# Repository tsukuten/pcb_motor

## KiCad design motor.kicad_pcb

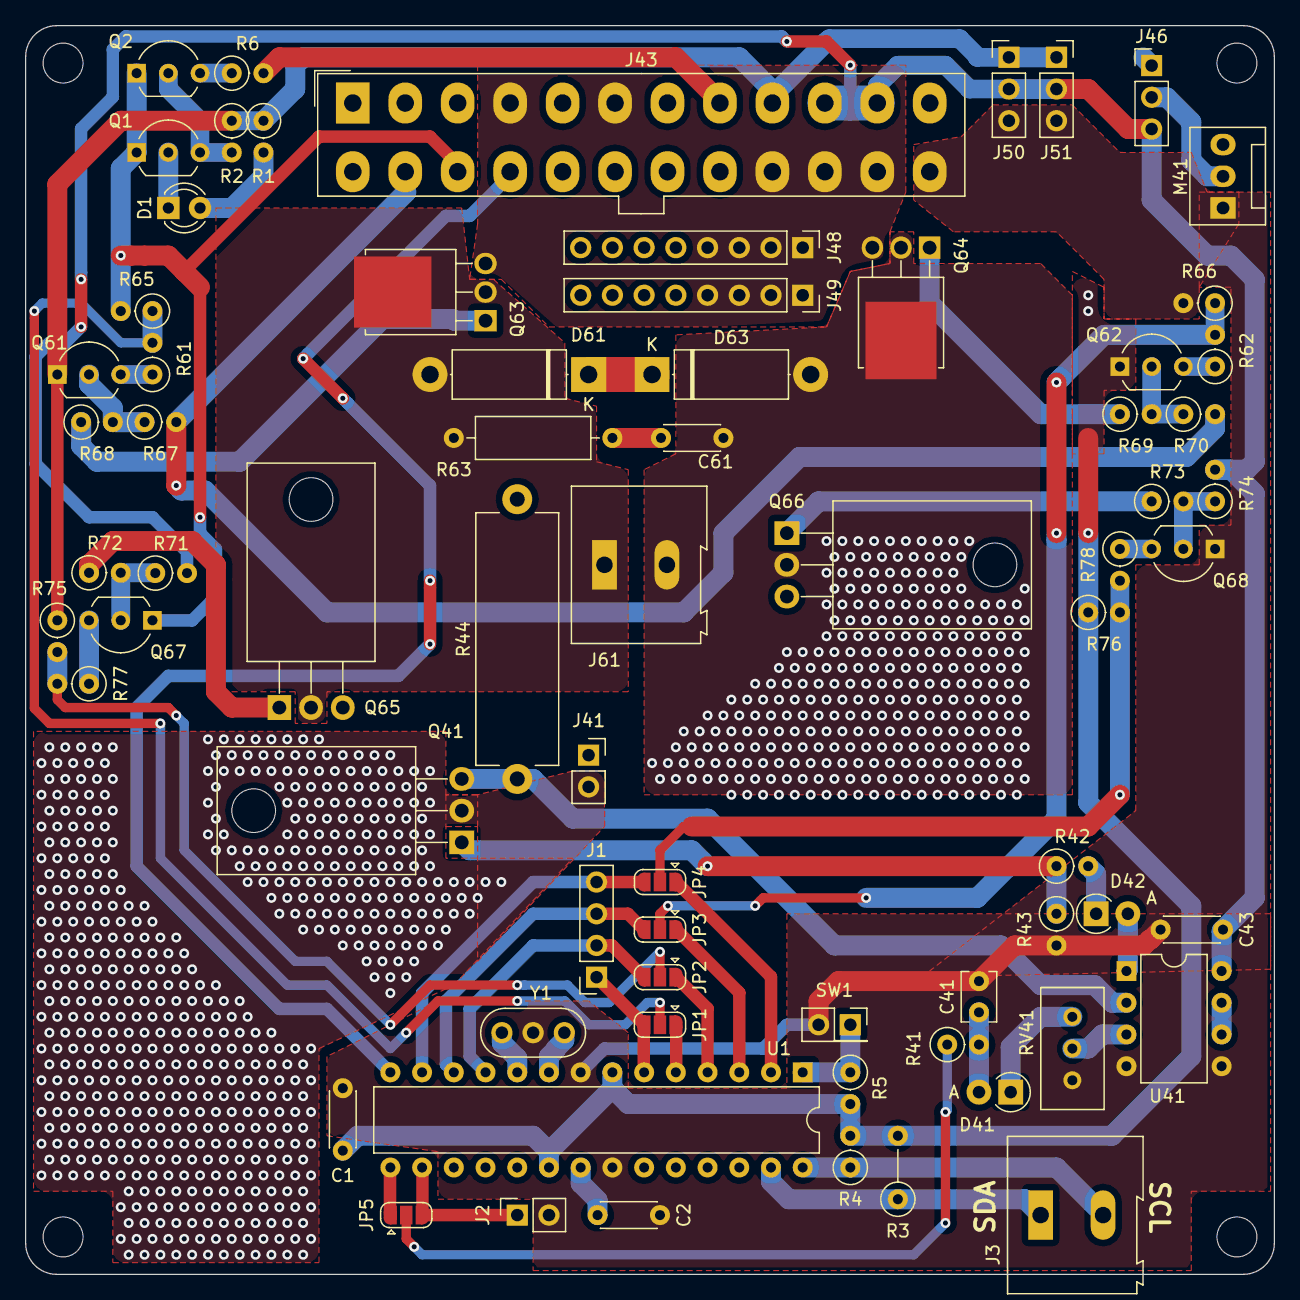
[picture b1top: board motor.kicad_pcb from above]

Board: 2 copper layers, 100.0 x 100.0 mm, 70 parts (0 on the bottom side), 59 nets.

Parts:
C1, C2, C43: 10u; C_Disc_D4.3mm_W1.9mm_P5.00mm
C41: 1u; C_Disc_D3.8mm_W2.6mm_P2.50mm
C61: C_snub_A; C_Disc_D4.3mm_W1.9mm_P5.00mm
D1: Power_NG; LED_D3.0mm
D41, D42: 1V0; D_T-1_P2.54mm_Vertical_AnodeUp
D61, D63: 1N5338B; D_5W_P12.70mm_Horizontal
J1: Gates_B; PinSocket_1x04_P2.54mm_Vertical
J2: PWM_B; PinSocket_1x02_P2.54mm_Vertical
J3: I2C; TerminalBlock_Altech_AK300-2_P5.00mm
J41: Jump_ID_A; PinSocket_1x02_P2.54mm_Vertical
J43: ATX_power; Molex_Mini-Fit_Jr_5566-24A_2x12_P4.20mm_Vertical
J46: Fan_vol_sel; PinHeader_1x03_P2.54mm_Vertical
J48: Power_male; PinHeader_1x08_P2.54mm_Vertical
J49: Power_female; PinSocket_1x08_P2.54mm_Vertical
J50: Power_signal_male; PinHeader_1x03_P2.54mm_Vertical
J51: Power_signal_female; PinSocket_1x03_P2.54mm_Vertical
J61: Motor_A; TerminalBlock_Altech_AK300-2_P5.00mm
JP1: Gate_sel_POS_P; SolderJumper-3_P1.3mm_Open_RoundedPad1.0x1.5mm
JP2: Gate_sel_POS_N; SolderJumper-3_P1.3mm_Open_RoundedPad1.0x1.5mm
JP3: Gate_sel_NEG_P; SolderJumper-3_P1.3mm_Open_RoundedPad1.0x1.5mm
JP4: Gate_sel_NEG_N; SolderJumper-3_P1.3mm_Open_RoundedPad1.0x1.5mm
JP5: PWM_sel; SolderJumper-3_P1.3mm_Open_RoundedPad1.0x1.5mm
M41: Fan_FET; FanPinHeader_1x03_P2.54mm_Vertical
Q1, Q2, Q67, Q68: 2SC1815; TO-92_Inline_Wide
Q41, Q65, Q66: EKI04027; TO-220-3_Horizontal_TabDown
Q61, Q62: 2SA1015; TO-92_Inline_Wide
Q63, Q64: IRFU5505; TO-251-3-1EP_Horizontal_TabDown
R1, R2, R6: 6k8; R_Axial_DIN0207_L6.3mm_D2.5mm_P2.54mm_Vertical
R3: 10k; R_Axial_DIN0207_L6.3mm_D2.5mm_P5.08mm_Vertical
R4, R5, R41, R67, R68, R69, R70, R71, R72, R73, R74: 10k; R_Axial_DIN0207_L6.3mm_D2.5mm_P2.54mm_Vertical
R42: 150; R_Axial_DIN0207_L6.3mm_D2.5mm_P2.54mm_Vertical
R43, R65, R66, R75, R76: 47k; R_Axial_DIN0207_L6.3mm_D2.5mm_P2.54mm_Vertical
R44: 0R33; R_Axial_Power_L20.0mm_W6.4mm_P22.40mm
R61, R62, R77, R78: 1k; R_Axial_DIN0207_L6.3mm_D2.5mm_P2.54mm_Vertical
R63: R_snub_A; R_Axial_DIN0309_L9.0mm_D3.2mm_P12.70mm_Horizontal
RV41: 10k; Potentiometer_Bourns_3296W_Vertical
SW1: Reset; PinSocket_2x01_P2.54mm_Vertical
U1: ATmega328P-PU; DIP-28_W7.62mm
U41: LM358; DIP-8_W7.62mm
Y1: 16MHz; Resonator-3Pin_W8.0mm_H3.5mm

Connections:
+5V: J43.4, J43.6, J43.21, J43.22, J43.23, J48.1, J48.2, J48.3, J48.4, J49.1, J49.2, J49.3, J49.4, Q63.3, Q64.3
+5VD: C1.1, J43.9, J46.1, J50.1, J51.1, Q61.1, Q62.1, R1.1, R2.1, R3.2, R4.2, R5.2, R75.1, R76.1, U1.7, U1.20
+12V: C43.1, J43.10, J43.11, J46.3, J50.2, J51.2, R71.2, R74.2, U41.8
-12V: J43.14, R67.2, R70.2
/Driver/Motor_A: D61.2, J61.1, Q63.2, Q63.4, Q65.2, R63.1
/Driver/Motor_~A~: C61.2, D63.2, J61.2, Q64.2, Q64.4, Q66.2
/Driver/V-: J41.1, Q65.3, Q66.3
/Gate_A_NEG_N: JP4.1, U1.2
/Gate_A_NEG_P: JP3.1, U1.3
/Gate_A_POS_N: JP2.1, U1.4
/Gate_A_POS_P: JP1.1, U1.5
/Gate_B_NEG_N: J1.4, JP4.3, U1.13
/Gate_B_NEG_P: J1.3, JP3.3, U1.12
/Gate_B_POS_N: J1.2, JP2.3, U1.11
/Gate_B_POS_P: J1.1, JP1.3, U1.6
/Gate_NEG_N: JP4.2, R76.2, R78.2
/Gate_NEG_P: JP3.2, R62.2, R66.1
/Gate_POS_N: JP2.2, R75.2, R77.2
/Gate_POS_P: JP1.2, R61.2, R65.1
/PWM: JP5.2, R41.1
/PWM_A: JP5.1, U1.15
/PWM_B: J2.1, JP5.3, U1.16
/PWR_OK: J43.8, R6.2
/SCL: J3.2, R4.1, U1.28
/SDA: J3.1, R3.1, U1.27
/~PS_ON~: J43.16, U1.14
GND: C1.2, C2.2, C41.2, C43.2, J2.2, J43.3, J43.5, J43.7, J43.15, J43.17, J43.18, J43.19, J43.24, J48.5, J48.6, J48.7, J48.8, J49.5, J49.6, J49.7, J49.8, J50.3, J51.3, M41.1, Q1.1, Q2.1, Q67.1, Q68.1, R43.2, R44.2, R65.2, R66.2, RV41.3, SW1.2, U1.8, U1.22, U41.4, U41.5, Y1.2
unnamed: C2.1, U1.21
unnamed: C41.1, D41.2, R41.2
unnamed: C61.1, R63.2
unnamed: D1.1, Q1.2
unnamed: D1.2, R1.2
unnamed: D41.1, RV41.1
unnamed: D42.1, R42.2
unnamed: D42.2, U41.1
unnamed: D61.1, D63.1
unnamed: J41.2, Q41.2
unnamed: J46.2, M41.2
unnamed: Q1.3, Q2.2, R2.2
unnamed: Q2.3, R6.1
unnamed: Q41.1, R42.1, R43.1
unnamed: Q41.3, R44.1, U41.2
unnamed: Q61.2, R67.1, R68.2
unnamed: Q61.3, R61.1
unnamed: Q62.2, R69.2, R70.1
unnamed: Q62.3, R62.1
unnamed: Q63.1, R68.1
unnamed: Q64.1, R69.1
unnamed: Q65.1, R72.1
unnamed: Q66.1, R73.1
unnamed: Q67.2, R71.1, R72.2
unnamed: Q67.3, R77.1
unnamed: Q68.2, R73.2, R74.1
unnamed: Q68.3, R78.1
unnamed: R5.1, SW1.1, U1.1
unnamed: RV41.2, U41.3
unnamed: U1.9, Y1.1
unnamed: U1.10, Y1.3
unnamed: U41.6, U41.7

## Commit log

2018-10-01 schematic: Add files
2018-10-01 Add .gitiginore
2018-10-01 schematic: Assign footprints to components
2018-10-02 schematic: Many fixes to have only one pole driver on a PCB
2018-10-02 schematic: Remove the heatsink
    The heatsinks sold by Akizuki is too tall.
2018-10-02 schematic: Use EKI04027 instead of FKI10531 for drivers for power dispassion
2018-10-02 schematic: Remove a redundant testing header
2018-10-02 schematic: Remove more redundant testing headers
2018-10-02 schematic: Change footprints for PCB
2018-10-02 Add a work-in-progress PCB file
2018-10-03 PCB: Update
2018-10-03 Do not connect PWR_OK to AVR
    It is too far! If you need it, connect it by your hand.
2018-10-03 PCB: Add solder masks as heat sinks
2018-10-03 PCB: Add vias to filled zones
2018-10-03 PCB: Add a copyright text
2018-10-03 PCB: Add/move silks
2018-10-04 Bump to v0.0.0

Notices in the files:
motor.kicad_pcb:
©2018 Tsukuba Univ. Astronomy Club
